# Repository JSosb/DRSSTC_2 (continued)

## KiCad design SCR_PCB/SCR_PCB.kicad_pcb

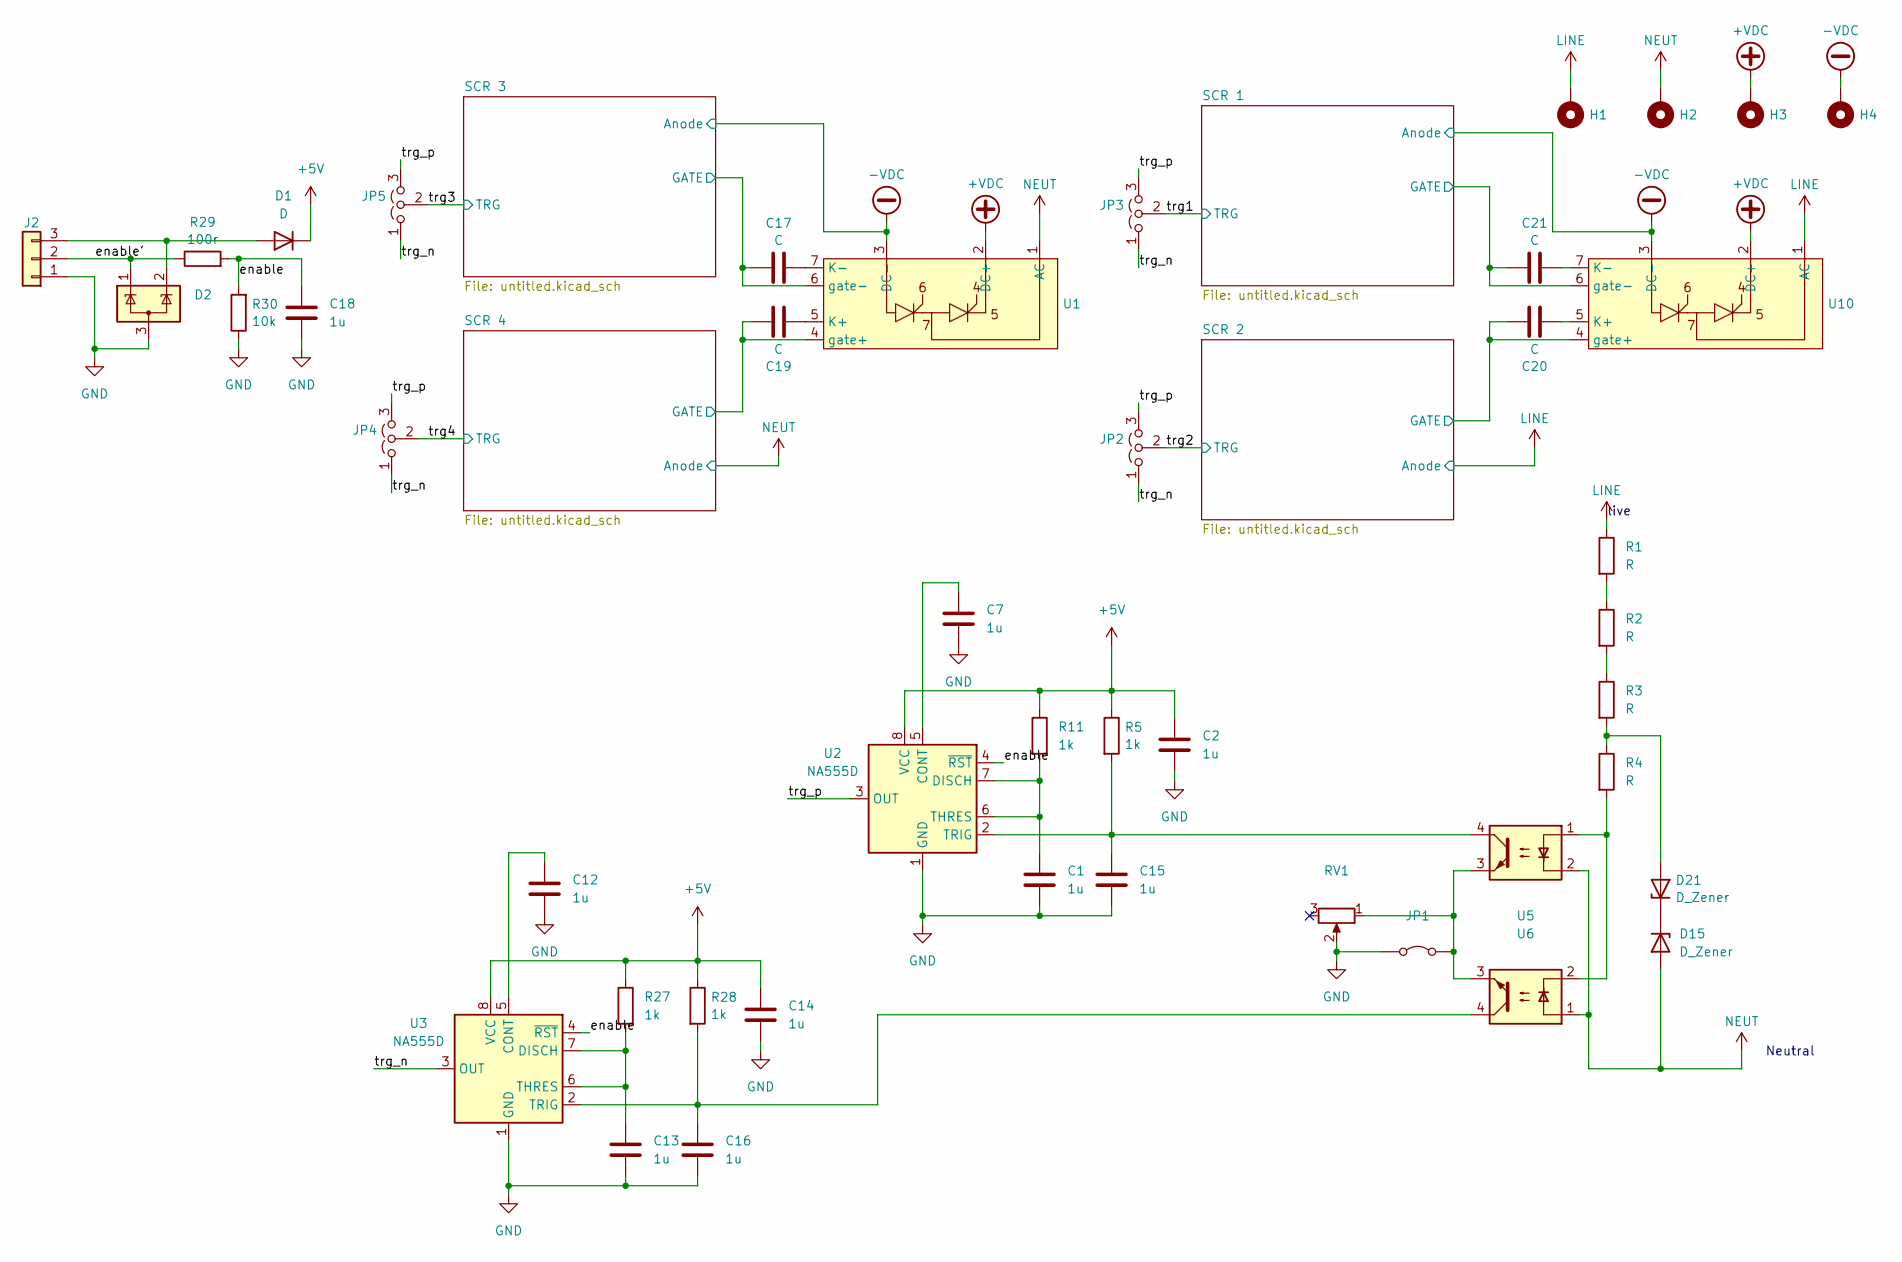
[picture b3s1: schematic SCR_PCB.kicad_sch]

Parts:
C1, C2, C7, C12, C13, C14, C15, C16, C18: 1u; C_0805_2012Metric
C17, C19, C20, C21: C; C_Axial_L5.1mm_D3.1mm_P15.00mm_Horizontal
D1: D; D_SMA
D2: SP0502BAHT; SOT-23
D15, D21: D_Zener; D_SMA
H1, H2, H3, H4: MountingHole_Pad; MountingHole_5.3mm_M5_Pad_Via
J2: Conn_01x03; Molex_SL_171971-0003_1x03_P2.54mm_Vertical
JP1: Jumper_2_Bridged; SolderJumper-2_P1.3mm_Bridged2Bar_RoundedPad1.0x1.5mm
JP2, JP3, JP4, JP5: Jumper_3_Open; SolderJumper-3_P1.3mm_Bridged2Bar123_RoundedPad1.0x1.5mm_Nu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
R1, R2, R3, R4: R; R_1206_3216Metric
R5, R11, R27, R28: 1k; R_0805_2012Metric
R29: 100r; R_0805_2012Metric
R30: 10k; R_0805_2012Metric
RV1: R_Potentiometer; Potentiometer_ACP_CA6-VSMD_Vertical
U1, U10: scr
U2, U3: NA555D; SOIC-8_3.9x4.9mm_P1.27mm
U5, U6: SFH617A-1; DIP-4_W7.62mm

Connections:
+5V: C2.1, C14.1, D1.1 (K), R5.1, R11.1, R27.1, R28.1, U2.8 (VCC), U3.8 (VCC)
+VDC: H3.1, U1.2 (DC+), U10.2 (DC+)
-VDC: H4.1, U1.3 (DC-), U10.3 (DC-); also elsewhere on the board
/SCR 1/GATE: C21.1, U10.6 (gate-); also elsewhere on the board
/SCR 2/GATE: C20.1, U10.4 (gate+); also elsewhere on the board
/SCR 3/GATE: C17.1, U1.6 (gate-); also elsewhere on the board
/SCR 4/GATE: C19.1, U1.4 (gate+); also elsewhere on the board
/enable: C18.1, R29.2, R30.2, U2.4 (~RST), U3.4 (~RST)
/enable': D2.1 (K), J2.2, R29.1
/trg1: JP3.2 (C); also elsewhere on the board
/trg2: JP2.2 (C); also elsewhere on the board
/trg3: JP5.2 (C); also elsewhere on the board
/trg4: JP4.2 (C); also elsewhere on the board
/trg_n: JP2.1 (A), JP3.1 (A), JP4.1 (A), JP5.1 (A), U3.3 (OUT)
/trg_p: JP2.3 (B), JP3.3 (B), JP4.3 (B), JP5.3 (B), U2.3 (OUT)
GND: C1.2, C2.2, C7.2, C12.2, C13.2, C14.2, C15.2, C16.2, C18.2, D2.3 (A), J2.1, JP1.1 (A), R30.1, RV1.2, U2.1 (GND), U3.1 (GND); also elsewhere on the board
LINE: H1.1, R1.1, U10.1 (AC); also elsewhere on the board
NEUT: D15.2 (A), H2.1, U1.1 (AC), U5.2, U6.1; also elsewhere on the board
unnamed: D1.2 (A), D2.2 (K), J2.3
unnamed: D15.1 (K), D21.1 (K)
unnamed: D21.2 (A), R3.2, R4.1
unnamed: JP1.2 (B), RV1.1, U5.3, U6.3
unnamed: R1.2, R2.1
unnamed: R2.2, R3.1
unnamed: R4.2, U5.1, U6.2
unnamed: C19.2, U1.5 (K+)
unnamed: C17.2, U1.7 (K-)
unnamed: C7.1, U2.5 (CONT)
unnamed: C1.1, R11.2, U2.6 (THRES), U2.7 (DISCH)
unnamed: C15.1, R5.2, U2.2 (TRIG), U5.4
unnamed: C12.1, U3.5 (CONT)
unnamed: C13.1, R27.2, U3.6 (THRES), U3.7 (DISCH)
unnamed: C16.1, R28.2, U3.2 (TRIG), U6.4
unnamed: C20.2, U10.5 (K+)
unnamed: C21.2, U10.7 (K-)

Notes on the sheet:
live
Neutral

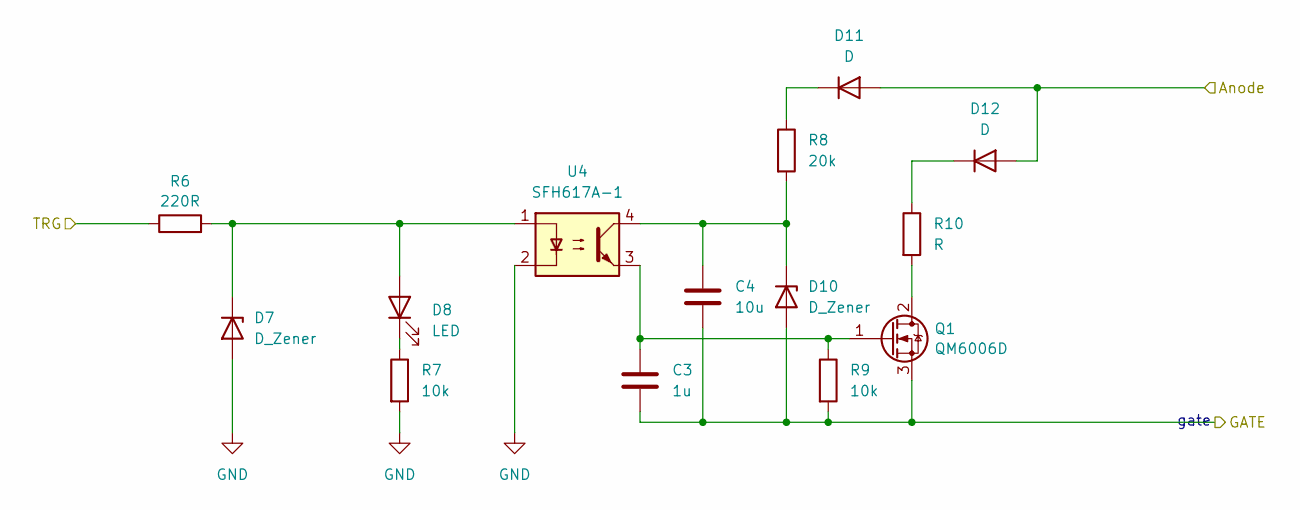
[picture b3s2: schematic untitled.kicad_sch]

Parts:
C3: 1u; C_0805_2012Metric
C4: 10u; C_0805_2012Metric
D7, D10: D_Zener; D_SMA
D8: LED; LED_1206_3216Metric
D11, D12: D; D_SMA
Q1: QM6006D; TO-252-2
R6: 220R; R_0805_2012Metric
R7, R9: 10k; R_0805_2012Metric
R8: 20k; R_Axial_DIN0207_L6.3mm_D2.5mm_P10.16mm_Horizontal
R10: R; R_Axial_DIN0918_L18.0mm_D9.0mm_P22.86mm_Horizontal
U4: SFH617A-1; DIP-4_W7.62mm

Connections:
-VDC: D11.2 (A), D12.2 (A); also elsewhere on the board
/SCR 1/GATE: C3.2, C4.2, D10.2 (A), Q1.3 (S), R9.2; also elsewhere on the board
/trg1: R6.1; also elsewhere on the board
GND: D7.2 (A), R7.2, U4.2; also elsewhere on the board
unnamed: D7.1 (K), D8.2 (A), R6.2, U4.1
unnamed: D8.1 (K), R7.1
unnamed: C4.1, D10.1 (K), R8.2, U4.4
unnamed: D11.1 (K), R8.1
unnamed: D12.1 (K), R10.1
unnamed: Q1.2 (D), R10.2
unnamed: C3.1, Q1.1 (G), R9.1, U4.3

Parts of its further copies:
C5, C8, C10: 1u; C_0805_2012Metric
C6, C9, C11: 10u; C_0805_2012Metric
D13, D16, D19, D22, D25, D28: D_Zener; D_SMA
D14, D20, D26: LED; LED_1206_3216Metric
D17, D18, D23, D24, D29, D30: D; D_SMA
Q2, Q3, Q4: QM6006D; TO-252-2
R12, R17, R22: 220R; R_0805_2012Metric
R13, R15, R18, R20, R23, R25: 10k; R_0805_2012Metric
R14, R19, R24: 20k; R_Axial_DIN0207_L6.3mm_D2.5mm_P10.16mm_Horizontal
R16, R21, R26: R; R_Axial_DIN0918_L18.0mm_D9.0mm_P22.86mm_Horizontal
U7, U8, U9: SFH617A-1; DIP-4_W7.62mm

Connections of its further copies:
-VDC: D23.2 (A), D24.2 (A); also elsewhere on the board
/SCR 2/GATE: C5.2, C6.2, D16.2 (A), Q2.3 (S), R15.2; also elsewhere on the board
/SCR 3/GATE: C8.2, C9.2, D22.2 (A), Q3.3 (S), R20.2; also elsewhere on the board
/SCR 4/GATE: C10.2, C11.2, D28.2 (A), Q4.3 (S), R25.2; also elsewhere on the board
/trg2: R12.1; also elsewhere on the board
/trg3: R17.1; also elsewhere on the board
/trg4: R22.1; also elsewhere on the board
GND: D13.2 (A), D19.2 (A), D25.2 (A), R13.2, R18.2, R23.2, U7.2, U8.2, U9.2; also elsewhere on the board
LINE: D17.2 (A), D18.2 (A); also elsewhere on the board
NEUT: D29.2 (A), D30.2 (A); also elsewhere on the board
unnamed: D13.1 (K), D14.2 (A), R12.2, U7.1
unnamed: D14.1 (K), R13.1
unnamed: C6.1, D16.1 (K), R14.2, U7.4
unnamed: D17.1 (K), R14.1
unnamed: D18.1 (K), R16.1
unnamed: D19.1 (K), D20.2 (A), R17.2, U8.1
unnamed: D20.1 (K), R18.1
unnamed: C9.1, D22.1 (K), R19.2, U8.4
unnamed: D23.1 (K), R19.1
unnamed: D24.1 (K), R21.1
unnamed: D25.1 (K), D26.2 (A), R22.2, U9.1
unnamed: D26.1 (K), R23.1
unnamed: C11.1, D28.1 (K), R24.2, U9.4
unnamed: D29.1 (K), R24.1
unnamed: D30.1 (K), R26.1
unnamed: Q2.2 (D), R16.2
unnamed: C5.1, Q2.1 (G), R15.1, U7.3
unnamed: Q3.2 (D), R21.2
unnamed: C8.1, Q3.1 (G), R20.1, U8.3
unnamed: Q4.2 (D), R26.2
unnamed: C10.1, Q4.1 (G), R25.1, U9.3

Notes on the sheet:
gate

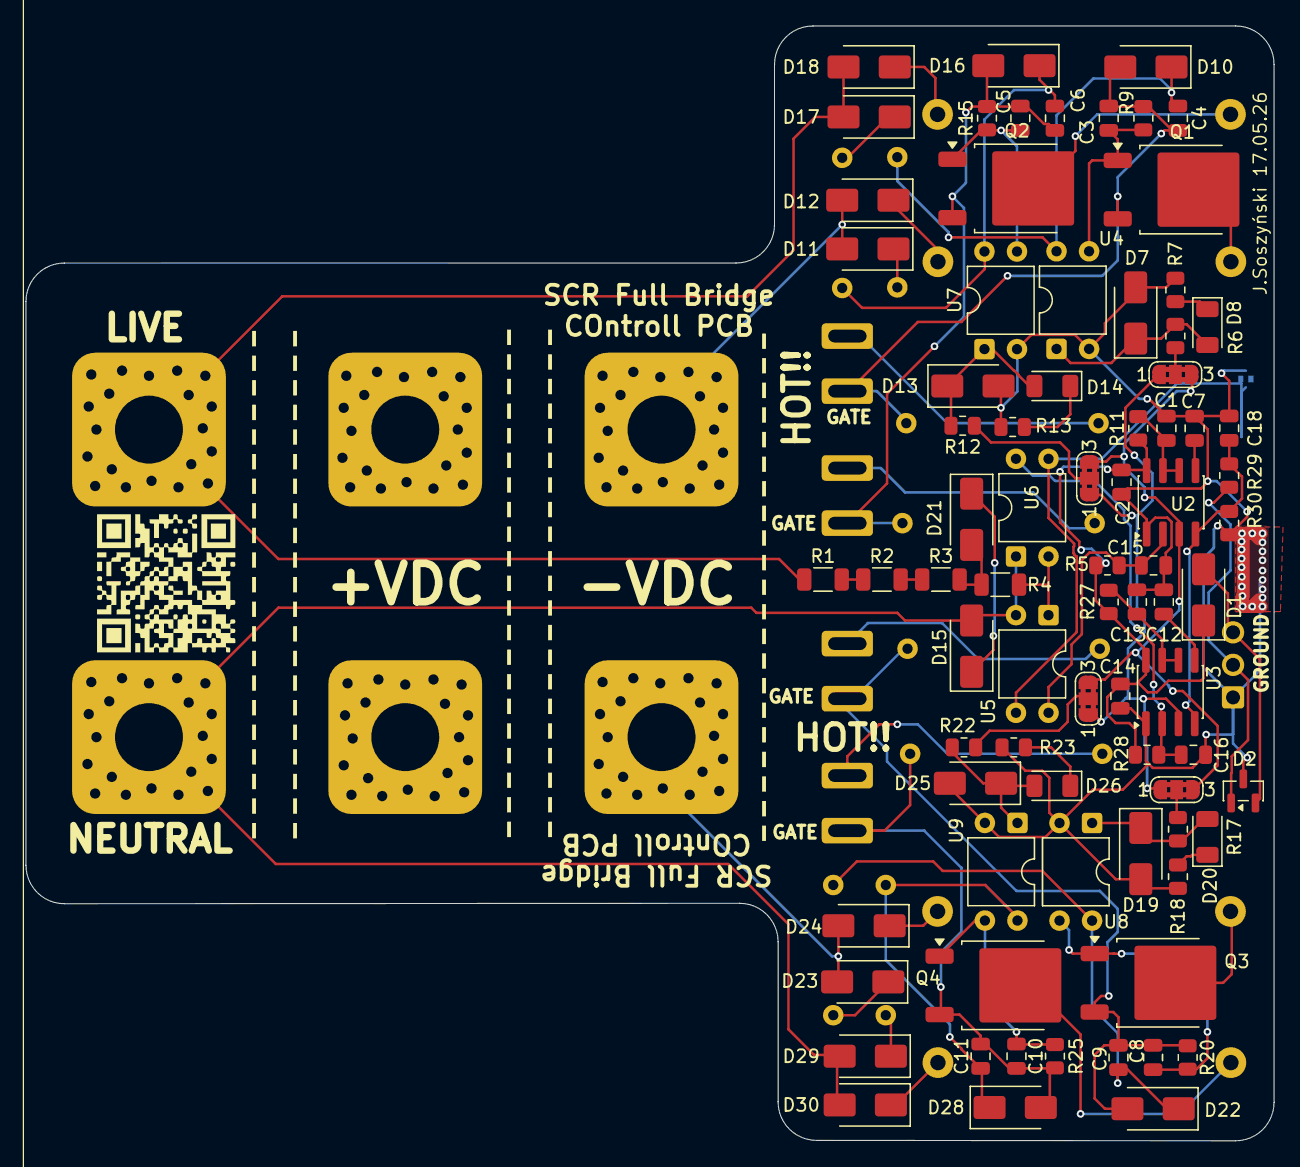
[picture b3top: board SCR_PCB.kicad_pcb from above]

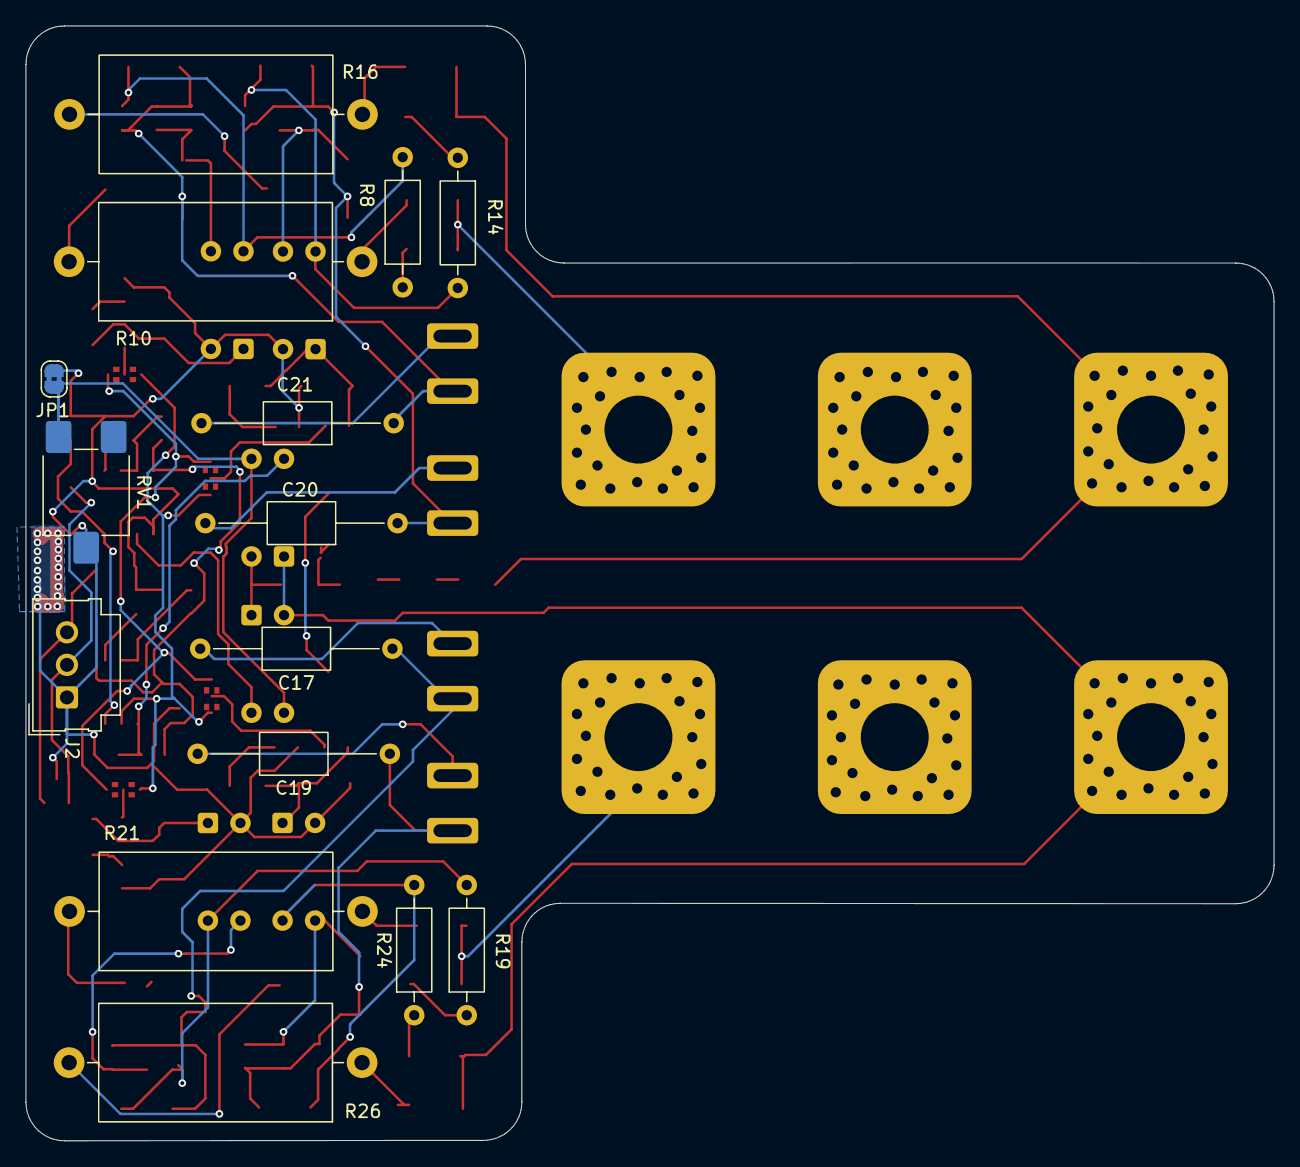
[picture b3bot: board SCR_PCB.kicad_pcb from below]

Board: 2 copper layers, 97.4 x 87.0 mm, 96 parts (15 on the bottom side), 63 nets.

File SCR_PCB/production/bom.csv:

Designator,Footprint,Quantity,Value,LCSC Part #
"_120, _119, _118, _117, _116, _115, _114, _113, _112, _111, _110, _109, _108, _107, _106, _105, _104, _103, _102, _101, _100, _99, _98, _97, _96, _95, _94, _93, _92, _91, _90, _89, _88, _87, _86, _85, _84, _83, _82, _81, _80, _79, _78, _77, _76, _75, _74, _73, _72, _71, _70, _69, _68, _67, _66, _65, _64, _63, _62, _61, _60, _59, _58, _57, _56, _55, _54, _53, _52, _51, _50, _49, _48, _47, _46, _45, _44, _43, _42, _41, _40, _39, _38, _37, _36, _35, _34, _33, _32, _31, _30, _29, _28, _27, _26, _25, _24, _23, _22, _21, _20, _19, _18, _17, _16, _15, _14, _13, _12, _11, _10, _9, _8, _7, _6, _5, _4, _3, _2, ",,120,,
"C1, C10, C12, C13, C14, C15, C16, C18, C2, C3, C5, C7, C8",0805,13,1u,
"C11, C4, C6, C9",0805,4,10u,
"C17, C19, C20, C21",C_Axial_L5.1mm_D3.1mm_P15.00mm_Horizontal,4,C,
"D1, D11, D12, D17, D18, D23, D24, D29, D30",D_SMA,9,D,
"D10, D13, D15, D16, D19, D21, D22, D25, D28, D7",D_SMA,10,D_Zener,
"D14, D20, D26, D8",1206,4,LED,
D2,SOT-23,1,SP0502BAHT,
J2,Molex_SL_171971-0003_1x03_P2.54mm_Vertical,1,Conn_01x03,
JP1,SolderJumper-2_P1.3mm_Bridged2Bar_RoundedPad1.0x1.5mm,1,Jumper_2_Bridged,
"Q1, Q2, Q3, Q4",TO-252-2,4,QM6006D,
"R1, R2, R3, R4",1206,4,R,
"R10, R16, R21, R26",R_Axial_DIN0918_L18.0mm_D9.0mm_P22.86mm_Horizontal,4,R,
"R11, R27, R28, R5",0805,4,1k,
"R12, R17, R22, R6",0805,4,220R,
"R13, R15, R18, R20, R23, R25, R30, R7, R9",0805,9,10k,
"R14, R19, R24, R8",R_Axial_DIN0207_L6.3mm_D2.5mm_P10.16mm_Horizontal,4,20k,
R29,0805,1,100r,
RV1,Potentiometer_ACP_CA6-VSMD_Vertical,1,R_Potentiometer,
"U1, U10",scr,2,~,
"U2, U3",SOIC-8_3.9x4.9mm_P1.27mm,2,NA555D,
"U4, U5, U6, U7, U8, U9",DIP-4_W7.62mm,6,SFH617A-1,

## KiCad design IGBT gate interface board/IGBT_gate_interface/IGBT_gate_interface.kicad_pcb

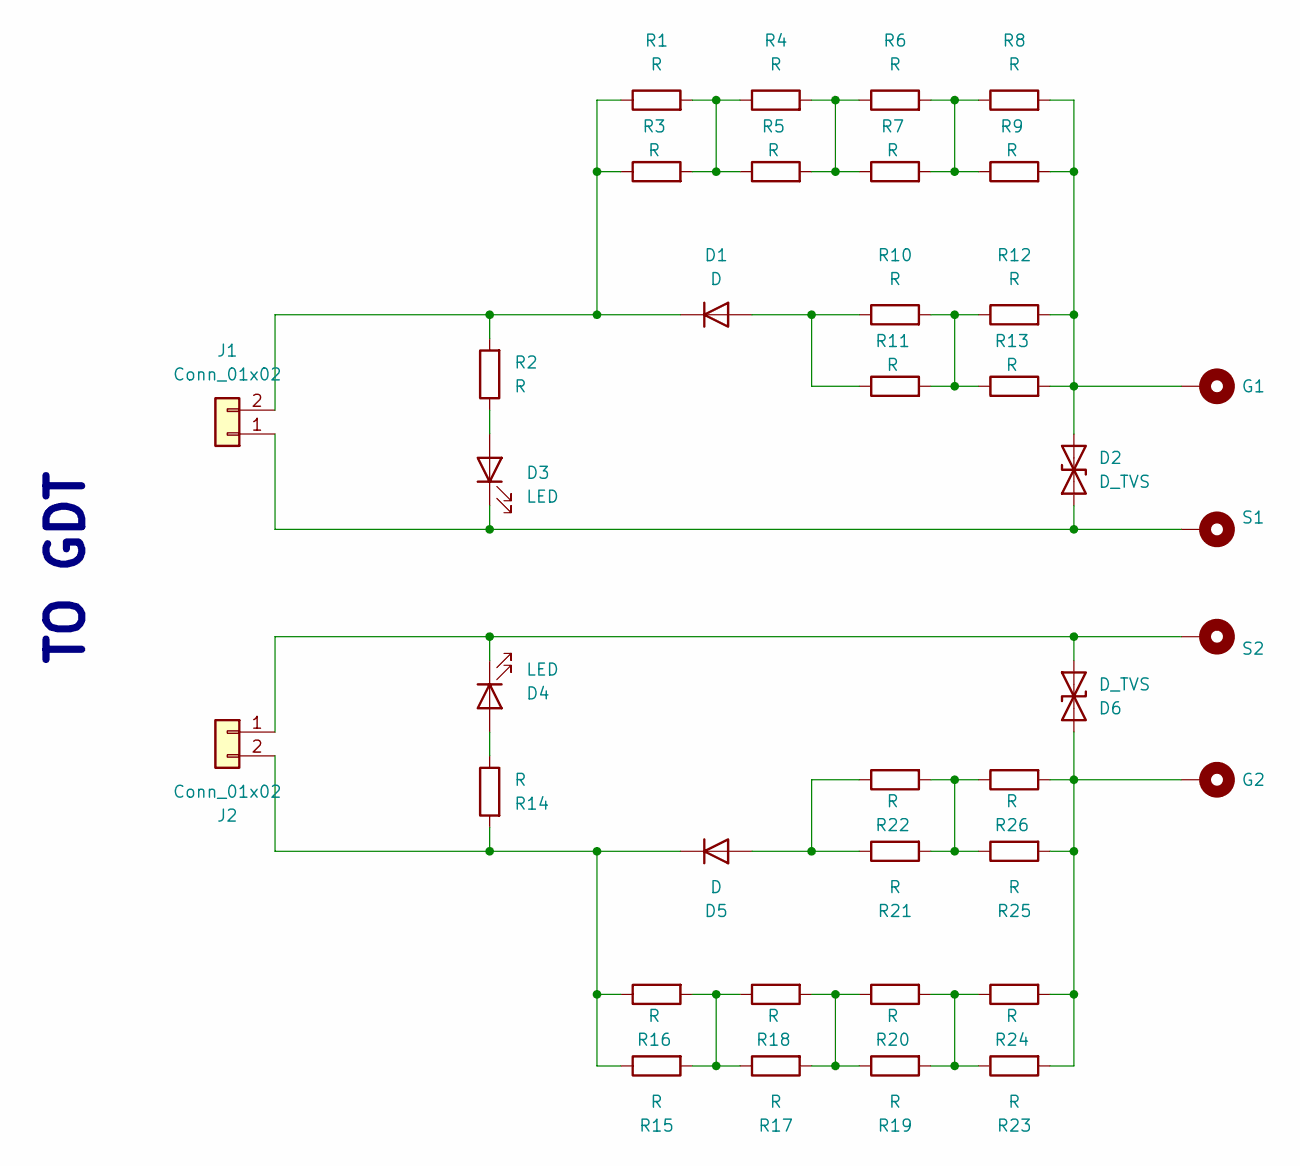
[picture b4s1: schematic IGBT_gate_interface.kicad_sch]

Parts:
D1, D5: D; D_SMB
D2, D6: D_TVS; D_SMB
D3, D4: LED; LED_1206_3216Metric
G1, G2: MountingHole_Pad; MountingHole_2.2mm_M2_DIN965_Pad
J1, J2: Conn_01x02; PinHeader_1x02_P2.54mm_Vertical
R1, R2, R3, R4, R5, R6, R7, R8, R9, R10, R11, R12, R13, R14, R15, R16, R17, R18, R19, R20, R21, R22, R23, R24, R25, R26: R; R_0805_2012Metric
S1, S2: MountingHole_Pad; MountingHole_2.2mm_M2_DIN965_Pad

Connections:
unnamed: D1.2 (A), R10.1, R11.1
unnamed: D1.1 (K), J1.2, R1.1, R2.2, R3.1
unnamed: D2.1 (A1), D3.1 (K), J1.1, S1.1
unnamed: D2.2 (A2), G1.1, R8.2, R9.2, R12.2, R13.2
unnamed: D3.2 (A), R2.1
unnamed: D4.2 (A), R14.1
unnamed: D4.1 (K), D6.1 (A1), J2.1, S2.1
unnamed: D5.2 (A), R21.1, R22.1
unnamed: D5.1 (K), J2.2, R14.2, R15.1, R16.1
unnamed: D6.2 (A2), G2.1, R23.2, R24.2, R25.2, R26.2
unnamed: R1.2, R3.2, R4.1, R5.1
unnamed: R4.2, R5.2, R6.1, R7.1
unnamed: R6.2, R7.2, R8.1, R9.1
unnamed: R10.2, R11.2, R12.1, R13.1
unnamed: R15.2, R16.2, R17.1, R18.1
unnamed: R17.2, R18.2, R19.1, R20.1
unnamed: R19.2, R20.2, R23.1, R24.1
unnamed: R21.2, R22.2, R25.1, R26.1

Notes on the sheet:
TO GDT

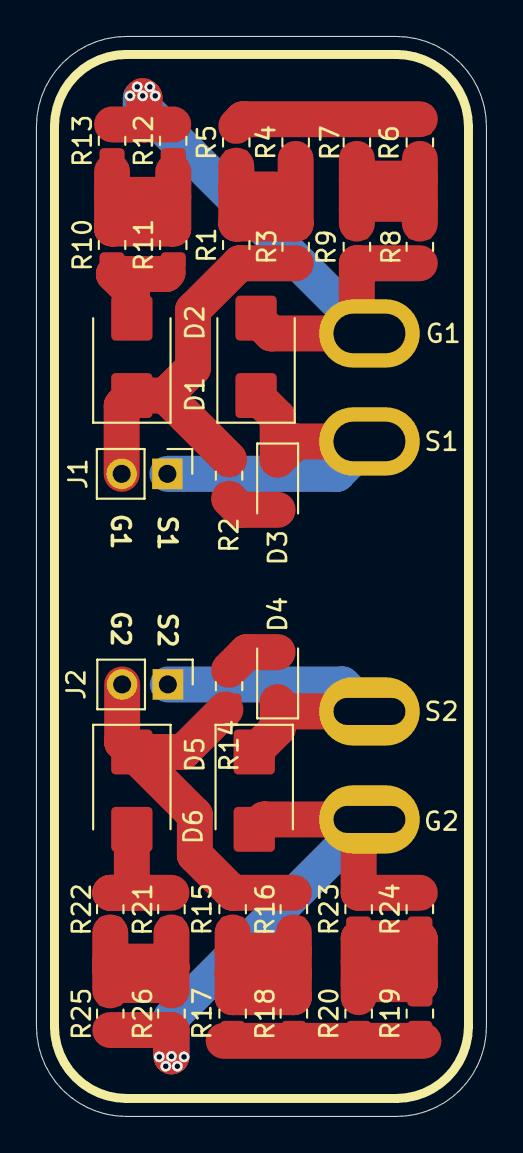
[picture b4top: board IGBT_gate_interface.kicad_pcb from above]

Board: 2 copper layers, 25.0 x 60.0 mm, 38 parts (0 on the bottom side), 18 nets.

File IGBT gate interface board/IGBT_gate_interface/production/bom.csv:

Designator,Footprint,Quantity,Value,LCSC Part #
"D1, D5",D_SMB,2,D,
"D2, D6",D_SMB,2,D_TVS,
"D3, D4",1206,2,LED,
"J1, J2",PinHeader_1x02_P2.54mm_Vertical,2,Conn_01x02,
"R1, R10, R11, R12, R13, R14, R15, R16, R17, R18, R19, R2, R20, R21, R22, R23, R24, R25, R26, R3, R4, R5, R6, R7, R8, R9",0805,26,R,

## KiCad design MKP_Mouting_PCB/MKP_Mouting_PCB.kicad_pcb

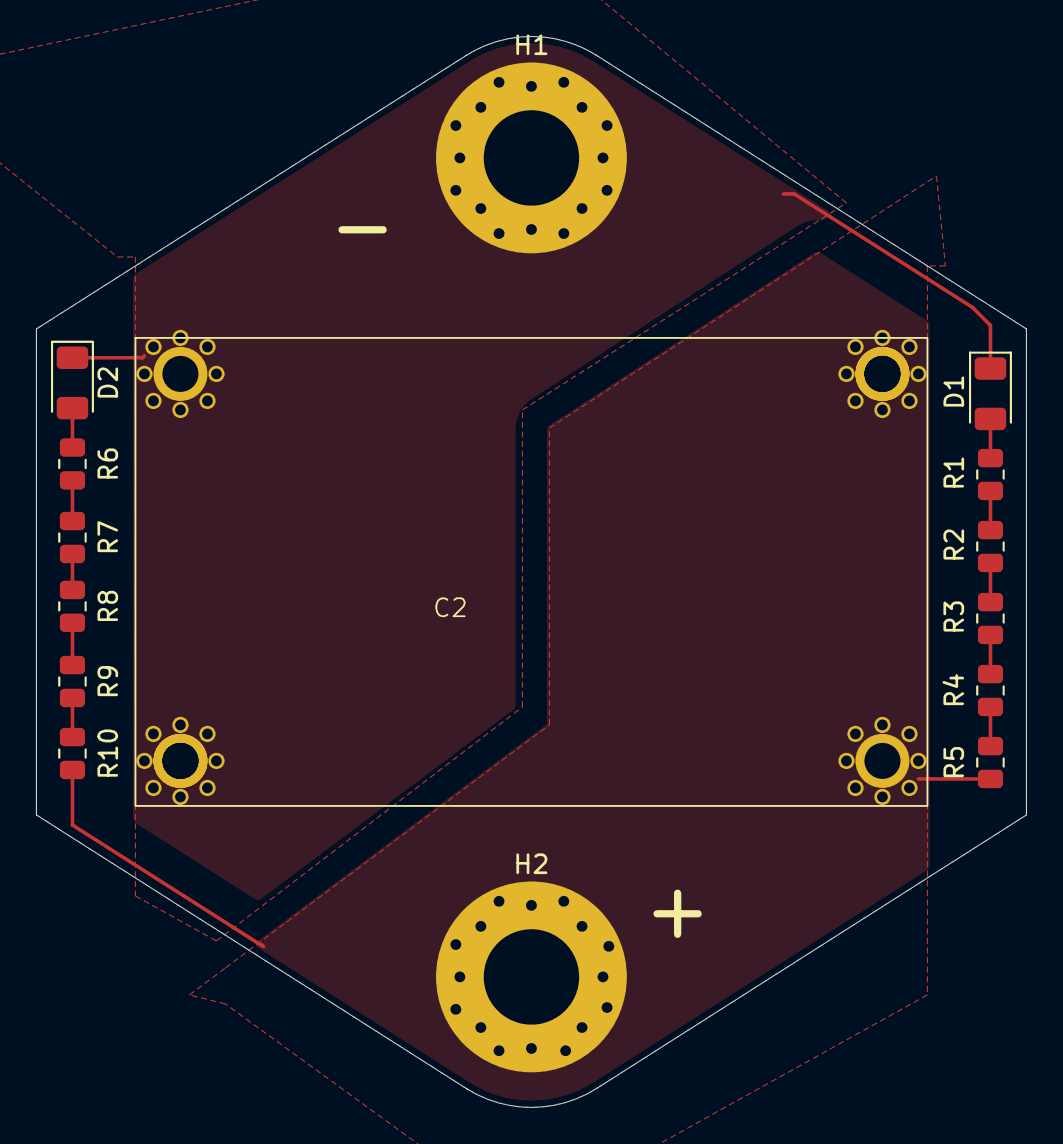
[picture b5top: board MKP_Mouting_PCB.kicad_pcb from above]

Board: 2 copper layers, 55.0 x 59.5 mm, 15 parts (0 on the bottom side), 12 nets.

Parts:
C2: mkp_cap
D1, D2: LED; LED_1206_3216Metric
H1, H2: MountingHole_Pad; MountingHole_5.3mm_M5_Pad_Via
R1, R2, R3, R4, R5, R6, R7, R8, R9, R10: R; R_0805_2012Metric

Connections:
unnamed: C2.3, H2.1 (1_1), R5.2, R10.2
unnamed: D1.2 (A), R1.1
unnamed: C2.1, C2.2, D1.1 (K), D2.1 (K), H1.1 (1_1)
unnamed: D2.2 (A), R6.1
unnamed: R1.2, R2.1
unnamed: R2.2, R3.1
unnamed: R3.2, R4.1
unnamed: R4.2, R5.1
unnamed: R6.2, R7.1
unnamed: R7.2, R8.1
unnamed: R8.2, R9.1
unnamed: R9.2, R10.1

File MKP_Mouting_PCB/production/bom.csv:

Designator,Footprint,Quantity,Value,LCSC Part #
"_50, _49, _48, _47, _46, _45, _44, _43, _42, _41, _40, _39, _38, _37, _36, _35, _34, _33, _32, _31, _30, _29, _28, _27, _26, _25, _24, _23, _22, _21, _20, _19, _18, _17, _16, _15, _14, _13, _12, _11, _10, _9, _8, _7, _6, _5, _4, _3, _2, ",,50,,
C2,mkp_cap,1,~,
"D1, D2",1206,2,LED,
"R1, R10, R2, R3, R4, R5, R6, R7, R8, R9",0805,10,R,

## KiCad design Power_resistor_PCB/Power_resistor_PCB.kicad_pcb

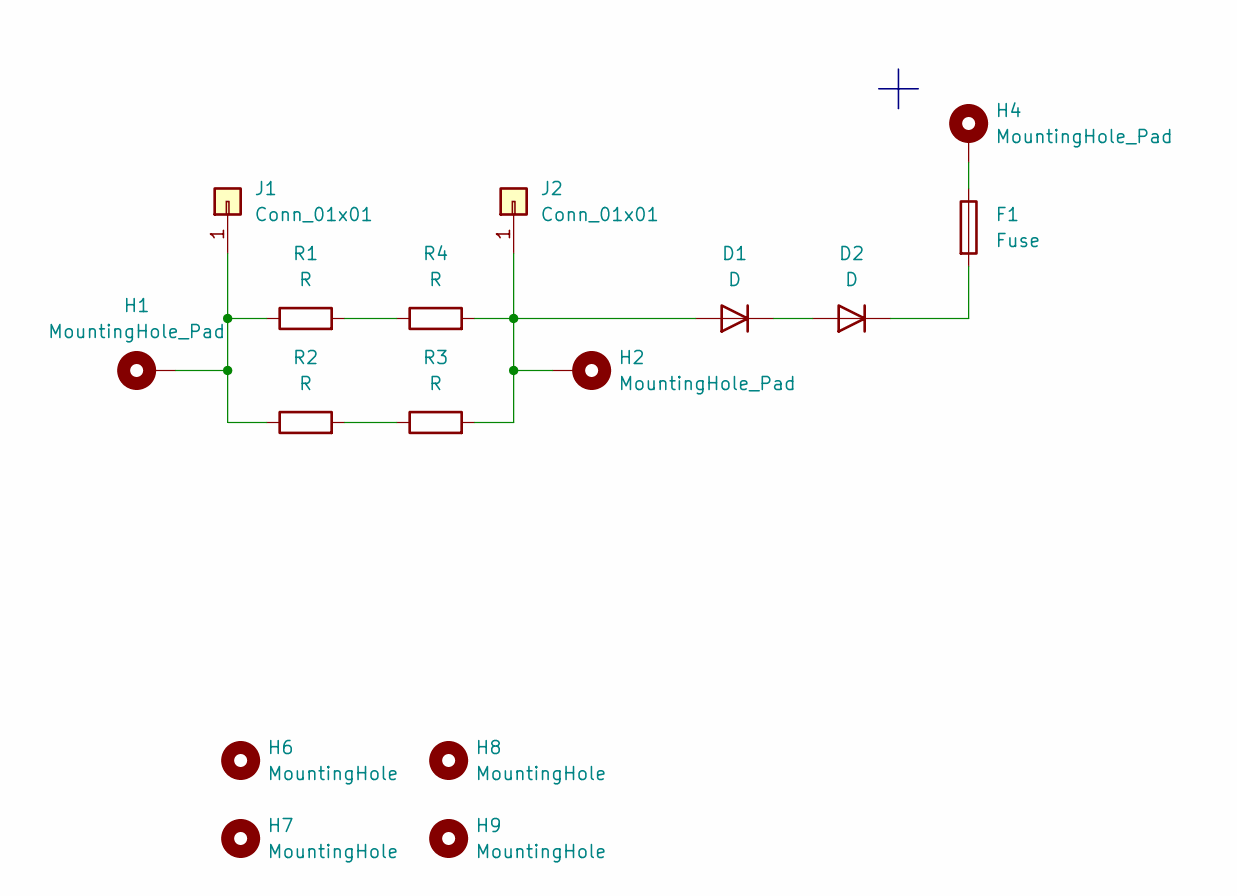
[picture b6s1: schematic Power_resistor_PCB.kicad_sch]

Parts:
D1, D2: D; D_SMA
F1: Fuse; Fuseholder_Clip-5x20mm_Keystone_3518P_Inline_P23.11x6.76mm_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
H1, H2, H4: MountingHole_Pad; MountingHole_3.2mm_M3_Pad_Via
H6, H7, H8, H9: MountingHole; MountingHole_3.2mm_M3
J1, J2: Conn_01x01; PinHeader_1x01_P2.54mm_Vertical
R1, R2, R3, R4: R; R_Axial_Power_L48.0mm_W12.5mm_P55.88mm

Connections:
unnamed: D1.2 (A), H2.1 (1_1), J2.1 (Pin_1_1), R3.2, R4.2
unnamed: D1.1 (K), D2.2 (A)
unnamed: D2.1 (K), F1.2
unnamed: F1.1, H4.1 (1_1)
unnamed: H1.1 (1_1), J1.1 (Pin_1_1), R1.1, R2.1
unnamed: R1.2, R4.1
unnamed: R2.2, R3.1

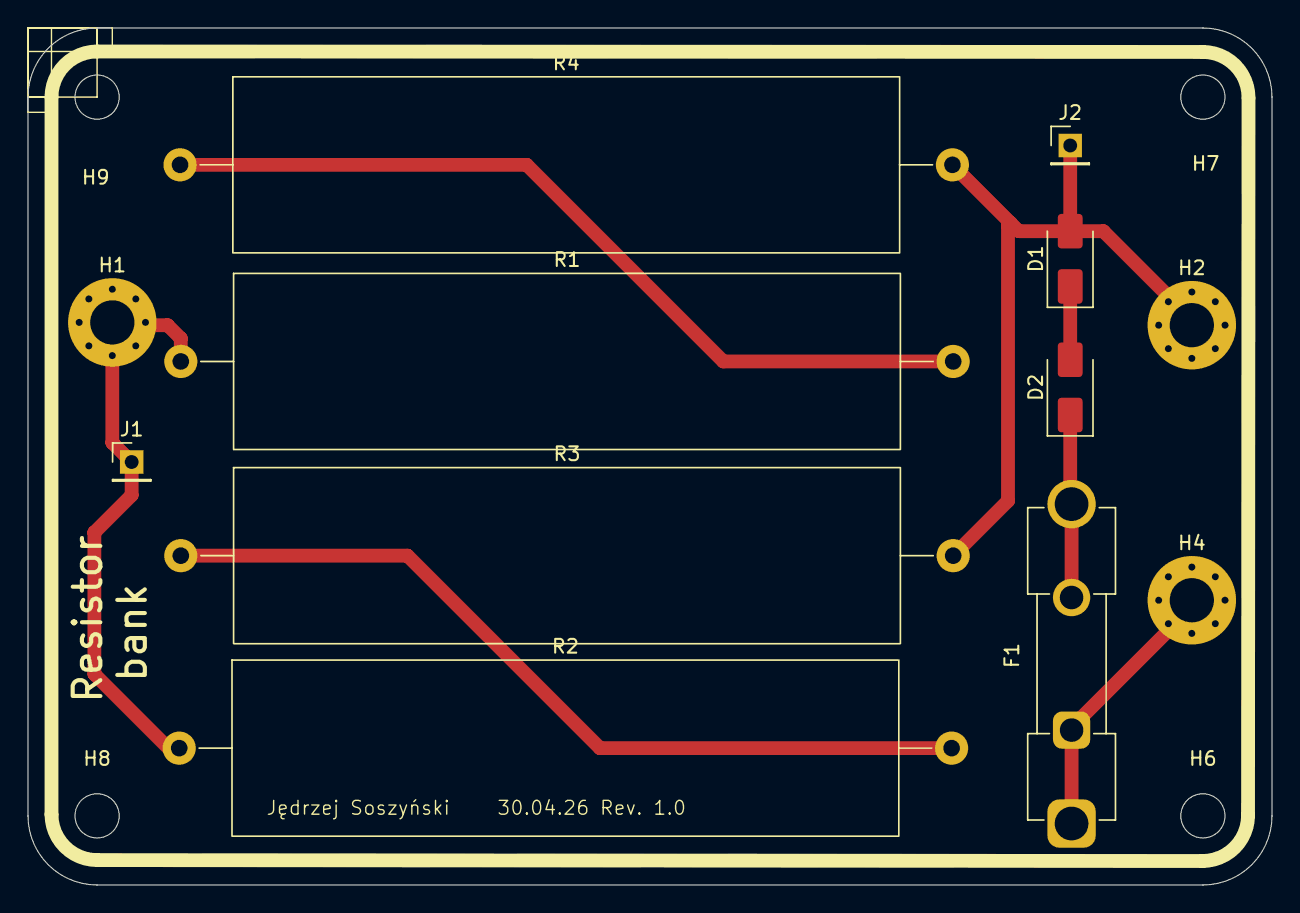
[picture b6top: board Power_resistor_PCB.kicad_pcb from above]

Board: 2 copper layers, 90.0 x 62.0 mm, 16 parts (0 on the bottom side), 7 nets.

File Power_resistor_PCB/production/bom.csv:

Designator,Footprint,Quantity,Value,LCSC Part #
"D1, D2",D_SMA,2,D,
F1,Fuseholder_Clip-5x20mm_Keystone_3518P_Inline_P23.11x6.76mm_D2.44x1.70mm_Horizontal,1,Fuse,
"J1, J2",PinHeader_1x01_P2.54mm_Vertical,2,Conn_01x01,
"R1, R2, R3, R4",R_Axial_Power_L48.0mm_W12.5mm_P55.88mm,4,R,

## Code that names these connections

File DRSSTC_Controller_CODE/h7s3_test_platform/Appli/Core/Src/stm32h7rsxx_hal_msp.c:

/* USER CODE BEGIN Header */
/**
  ******************************************************************************
  * @file         stm32h7rsxx_hal_msp.c
  * @brief        This file provides code for the MSP Initialization
  *               and de-Initialization codes.
  ******************************************************************************
  * @attention
  *
  * Copyright (c) 2026 STMicroelectronics.
  * All rights reserved.
  *
  * This software is licensed under terms that can be found in the LICENSE file
  * in the root directory of this software component.
  * If no LICENSE file comes with this software, it is provided AS-IS.
  *
  ******************************************************************************
  */
/* USER CODE END Header */

/* Includes ------------------------------------------------------------------*/
#include "main.h"
/* USER CODE BEGIN Includes */

/* USER CODE END Includes */

/* Private typedef -----------------------------------------------------------*/
/* USER CODE BEGIN TD */

/* USER CODE END TD */

/* Private define ------------------------------------------------------------*/
/* USER CODE BEGIN Define */

/* USER CODE END Define */

/* Private macro -------------------------------------------------------------*/
/* USER CODE BEGIN Macro */

/* USER CODE END Macro */

/* Private variables ---------------------------------------------------------*/
/* USER CODE BEGIN PV */

/* USER CODE END PV */

/* Private function prototypes -----------------------------------------------*/
/* USER CODE BEGIN PFP */

/* USER CODE END PFP */

/* External functions --------------------------------------------------------*/
/* USER CODE BEGIN ExternalFunctions */

/* USER CODE END ExternalFunctions */

/* USER CODE BEGIN 0 */

/* USER CODE END 0 */

void HAL_TIM_MspPostInit(TIM_HandleTypeDef *htim);
                    /**
  * Initializes the Global MSP.
  */
void HAL_MspInit(void)
{

  /* USER CODE BEGIN MspInit 0 */

  /* USER CODE END MspInit 0 */

  /* System interrupt init*/

  HAL_PWREx_EnableUSBHSregulator();

  /* USER CODE BEGIN MspInit 1 */

  /* USER CODE END MspInit 1 */
}

/**
  * @brief TIM_Base MSP Initialization
  * This function configures the hardware resources used in this example
  * @param htim_base: TIM_Base handle pointer
  * @retval None
  */
void HAL_TIM_Base_MspInit(TIM_HandleTypeDef* htim_base)
{
  GPIO_InitTypeDef GPIO_InitStruct = {0};
  if(htim_base->Instance==TIM1)
  {
    /* USER CODE BEGIN TIM1_MspInit 0 */

    /* USER CODE END TIM1_MspInit 0 */
    /* Peripheral clock enable */
    __HAL_RCC_TIM1_CLK_ENABLE();

    __HAL_RCC_GPIOC_CLK_ENABLE();
    __HAL_RCC_GPIOA_CLK_ENABLE();
    /**TIM1 GPIO Configuration
    PC10     ------> TIM1_BKIN
    PA12     ------> TIM1_ETR
    */
    GPIO_InitStruct.Pin = GPIO_PIN_10;
    GPIO_InitStruct.Mode = GPIO_MODE_AF_OD;
    GPIO_InitStruct.Pull = GPIO_NOPULL;
    GPIO_InitStruct.Speed = GPIO_SPEED_FREQ_LOW;
    GPIO_InitStruct.Alternate = GPIO_AF1_TIM1;
    HAL_GPIO_Init(GPIOC, &GPIO_InitStruct);

    GPIO_InitStruct.Pin = ZCD_Pin;
    GPIO_InitStruct.Mode = GPIO_MODE_AF_PP;
    GPIO_InitStruct.Pull = GPIO_PULLUP;
    GPIO_InitStruct.Speed = GPIO_SPEED_FREQ_VERY_HIGH;
    GPIO_InitStruct.Alternate = GPIO_AF1_TIM1;
    HAL_GPIO_Init(ZCD_GPIO_Port, &GPIO_InitStruct);

    /* TIM1 interrupt Init */
    HAL_NVIC_SetPriority(TIM1_BRK_IRQn, 0, 0);
    HAL_NVIC_EnableIRQ(TIM1_BRK_IRQn);
    HAL_NVIC_SetPriority(TIM1_UP_IRQn, 0, 0);
    HAL_NVIC_EnableIRQ(TIM1_UP_IRQn);
    /* USER CODE BEGIN TIM1_MspInit 1 */

    /* USER CODE END TIM1_MspInit 1 */
  }
  else if(htim_base->Instance==TIM2)
  {
    /* USER CODE BEGIN TIM2_MspInit 0 */

    /* USER CODE END TIM2_MspInit 0 */
    /* Peripheral clock enable */
    __HAL_RCC_TIM2_CLK_ENABLE();
    /* TIM2 interrupt Init */
    HAL_NVIC_SetPriority(TIM2_IRQn, 1, 0);
    HAL_NVIC_EnableIRQ(TIM2_IRQn);
    /* USER CODE BEGIN TIM2_MspInit 1 */

    /* USER CODE END TIM2_MspInit 1 */
  }

}

void HAL_TIM_MspPostInit(TIM_HandleTypeDef* htim)
{
  GPIO_InitTypeDef GPIO_InitStruct = {0};
  if(htim->Instance==TIM1)
  {
    /* USER CODE BEGIN TIM1_MspPostInit 0 */

    /* USER CODE END TIM1_MspPostInit 0 */

    __HAL_RCC_GPIOA_CLK_ENABLE();
    __HAL_RCC_GPIOB_CLK_ENABLE();
    /**TIM1 GPIO Configuration
    PA9     ------> TIM1_CH2
    PA8     ------> TIM1_CH1
    PB13     ------> TIM1_CH1N
    PB0     ------> TIM1_CH2N
    */
    GPIO_InitStruct.Pin = GPIO_PIN_9|GPIO_PIN_8;
    GPIO_InitStruct.Mode = GPIO_MODE_AF_PP;
    GPIO_InitStruct.Pull = GPIO_NOPULL;
    GPIO_InitStruct.Speed = GPIO_SPEED_FREQ_VERY_HIGH;
    GPIO_InitStruct.Alternate = GPIO_AF1_TIM1;
    HAL_GPIO_Init(GPIOA, &GPIO_InitStruct);

    GPIO_InitStruct.Pin = GPIO_PIN_13|GPIO_PIN_0;
    GPIO_InitStruct.Mode = GPIO_MODE_AF_PP;
    GPIO_InitStruct.Pull = GPIO_NOPULL;
    GPIO_InitStruct.Speed = GPIO_SPEED_FREQ_VERY_HIGH;
    GPIO_InitStruct.Alternate = GPIO_AF1_TIM1;
    HAL_GPIO_Init(GPIOB, &GPIO_InitStruct);

    /* USER CODE BEGIN TIM1_MspPostInit 1 */

    /* USER CODE END TIM1_MspPostInit 1 */
  }

}
/**
  * @brief TIM_Base MSP De-Initialization
  * This function freeze the hardware resources used in this example
  * @param htim_base: TIM_Base handle pointer
  * @retval None
  */
void HAL_TIM_Base_MspDeInit(TIM_HandleTypeDef* htim_base)
{
  if(htim_base->Instance==TIM1)
  {
    /* USER CODE BEGIN TIM1_MspDeInit 0 */

    /* USER CODE END TIM1_MspDeInit 0 */
    /* Peripheral clock disable */
    __HAL_RCC_TIM1_CLK_DISABLE();

    /**TIM1 GPIO Configuration
    PC10     ------> TIM1_BKIN
    PA12     ------> TIM1_ETR
    PA9     ------> TIM1_CH2
    PA8     ------> TIM1_CH1
    PB13     ------> TIM1_CH1N
    PB0     ------> TIM1_CH2N
    */
    HAL_GPIO_DeInit(GPIOC, GPIO_PIN_10);

    HAL_GPIO_DeInit(GPIOA, ZCD_Pin|GPIO_PIN_9|GPIO_PIN_8);

    HAL_GPIO_DeInit(GPIOB, GPIO_PIN_13|GPIO_PIN_0);

    /* TIM1 interrupt DeInit */
    HAL_NVIC_DisableIRQ(TIM1_BRK_IRQn);
    HAL_NVIC_DisableIRQ(TIM1_UP_IRQn);
    /* USER CODE BEGIN TIM1_MspDeInit 1 */

    /* USER CODE END TIM1_MspDeInit 1 */
  }
  else if(htim_base->Instance==TIM2)
  {
    /* USER CODE BEGIN TIM2_MspDeInit 0 */

    /* USER CODE END TIM2_MspDeInit 0 */
    /* Peripheral clock disable */
    __HAL_RCC_TIM2_CLK_DISABLE();

    /* TIM2 interrupt DeInit */
    HAL_NVIC_DisableIRQ(TIM2_IRQn);
    /* USER CODE BEGIN TIM2_MspDeInit 1 */

    /* USER CODE END TIM2_MspDeInit 1 */
  }

}

/* USER CODE BEGIN 1 */

/* USER CODE END 1 */

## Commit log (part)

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2026-05-06 init repo
2026-05-06 update SRC_PCB
2026-05-17 add SCR PCB
2026-05-17 Coplete SCR PCB
2026-05-26 start Controller schematic
2026-05-27 update the feedback stage simulation & controller schematic
2026-06-07 update conroller schematics
2026-06-15 assign footprints
2026-06-15 create controller layout
2026-06-16 refine conroller layout
2026-06-18 start cintrollenr routing
